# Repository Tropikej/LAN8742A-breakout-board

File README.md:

<h1 align="center">LAN8742A-breakout-board</h1>

<p align="center" width="100%">
  
</p>

***

<p align="center">
  
&nbsp; &nbsp; &nbsp; &nbsp;
  
</p>

***

## SPECIFICATIONS

| Parameter | Value | 
| --- | --- |
| Dimensions | 40.0 × 50.0 mm |

***

## DIRECTORY STRUCTURE

    .
    ├─ Computations       # Misc calculations
    ├─ HTML               # HTML files for generated webpage
    ├─ Images             # Pictures and renders
    │
    ├─ kibot_resources    # External resources for KiBot
    │  ├─ colors          # Color theme for KiCad
    │  ├─ fonts           # Fonts used in the project
    │  ├─ scripts         # External scripts used with KiBot
    │  └─ templates       # Templates for KiBot generated reports
    │
    ├─ kibot_yaml         # KiBot YAML config files
    ├─ KiRI               # KiRI (PCB diff viewer) files
    │
    ├─ lib                # KiCad footprint and symbol libraries
    │  ├─ 3d_models       # Component 3D models
    │  ├─ lib_fp          # Footprint libraries
    │  └─ lib_sym         # Symbol libraries
    │
    ├─ Logos              # Logos
    │
    ├─ Manufacturing      # Assembly and fabrication documents
    │  ├─ Assembly        # Assembly documents (BoM, pos, notes)
    │  │
    │  └─ Fabrication     # Fabrication documents (ZIP, notes)
    │     ├─ Drill Tables # CSV drill tables
    │     └─ Gerbers      # Gerbers
    │
    ├─ Report             # Reports for ERC/DRC
    ├─ Schematic          # PDF of schematic
    ├─ Templates          # Title block templates
    ├─ Testing
    │  └─ Testpoints      # Testpoints tables      
    │
    └─ Variants           # Outputs for assembly variants

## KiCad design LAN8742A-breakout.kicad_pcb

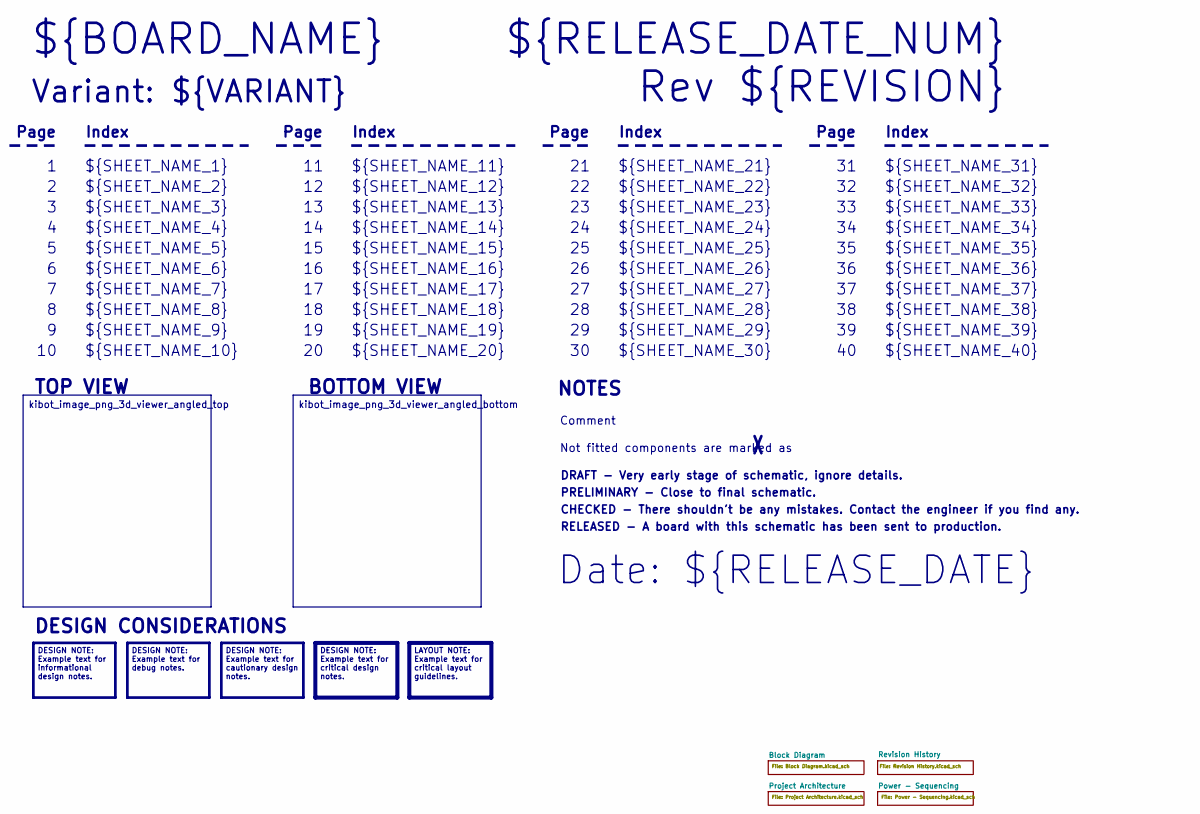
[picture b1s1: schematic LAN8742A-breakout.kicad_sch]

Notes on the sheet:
DESIGN NOTE: Example text for cautionary design notes.
DESIGN NOTE: Example text for debug notes.
DESIGN NOTE: Example text for critical design notes.
LAYOUT NOTE: Example text for critical layout guidelines.
kibot_image_png_3d_viewer_angled_bottom
DESIGN NOTE: Example text for informational design notes.
kibot_image_png_3d_viewer_angled_top
Variant: ${VARIANT}
RELEASED - A board with this schematic has been sent to production.
${SHEET_NAME_24}
Index
Page
PRELIMINARY - Close to final schematic.
${SHEET_NAME_22}
DRAFT - Very early stage of schematic, ignore details.
${SHEET_NAME_12}
${SHEET_NAME_8}
${SHEET_NAME_2}
${SHEET_NAME_5}
${SHEET_NAME_20}
${SHEET_NAME_23}
${RELEASE_DATE_NUM}
${SHEET_NAME_35}
Not fitted components are marked as
${SHEET_NAME_11}
${SHEET_NAME_6}
${SHEET_NAME_37}
${SHEET_NAME_26}
${SHEET_NAME_36}
Rev ${REVISION}
${SHEET_NAME_15}
CHECKED - There shouldn't be any mistakes. Contact the engineer if you find any.
BOTTOM VIEW
${SHEET_NAME_14}
${SHEET_NAME_21}
${SHEET_NAME_17}
${SHEET_NAME_18}
Date: ${RELEASE_DATE}
${SHEET_NAME_7}
${SHEET_NAME_31}

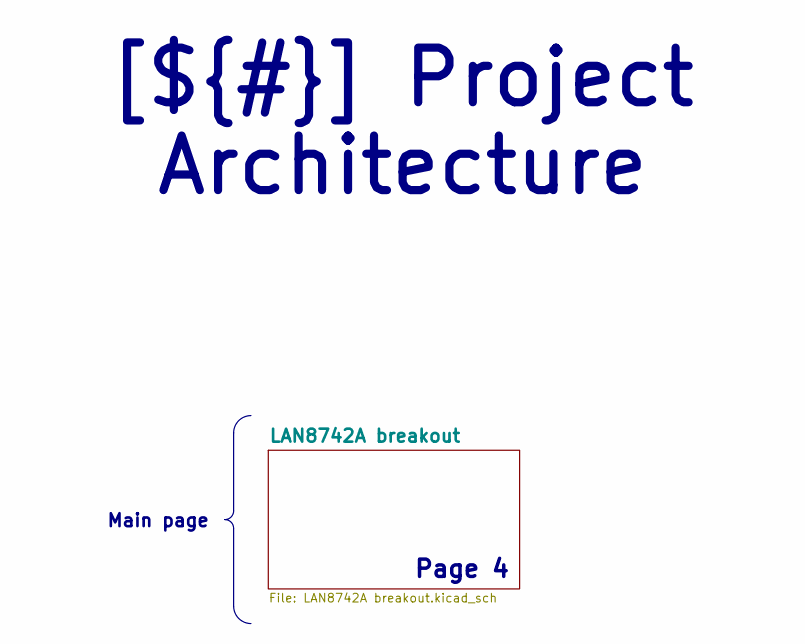
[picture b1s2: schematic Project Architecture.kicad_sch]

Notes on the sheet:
Main page
[${#}] ${TITLE}
Page 4

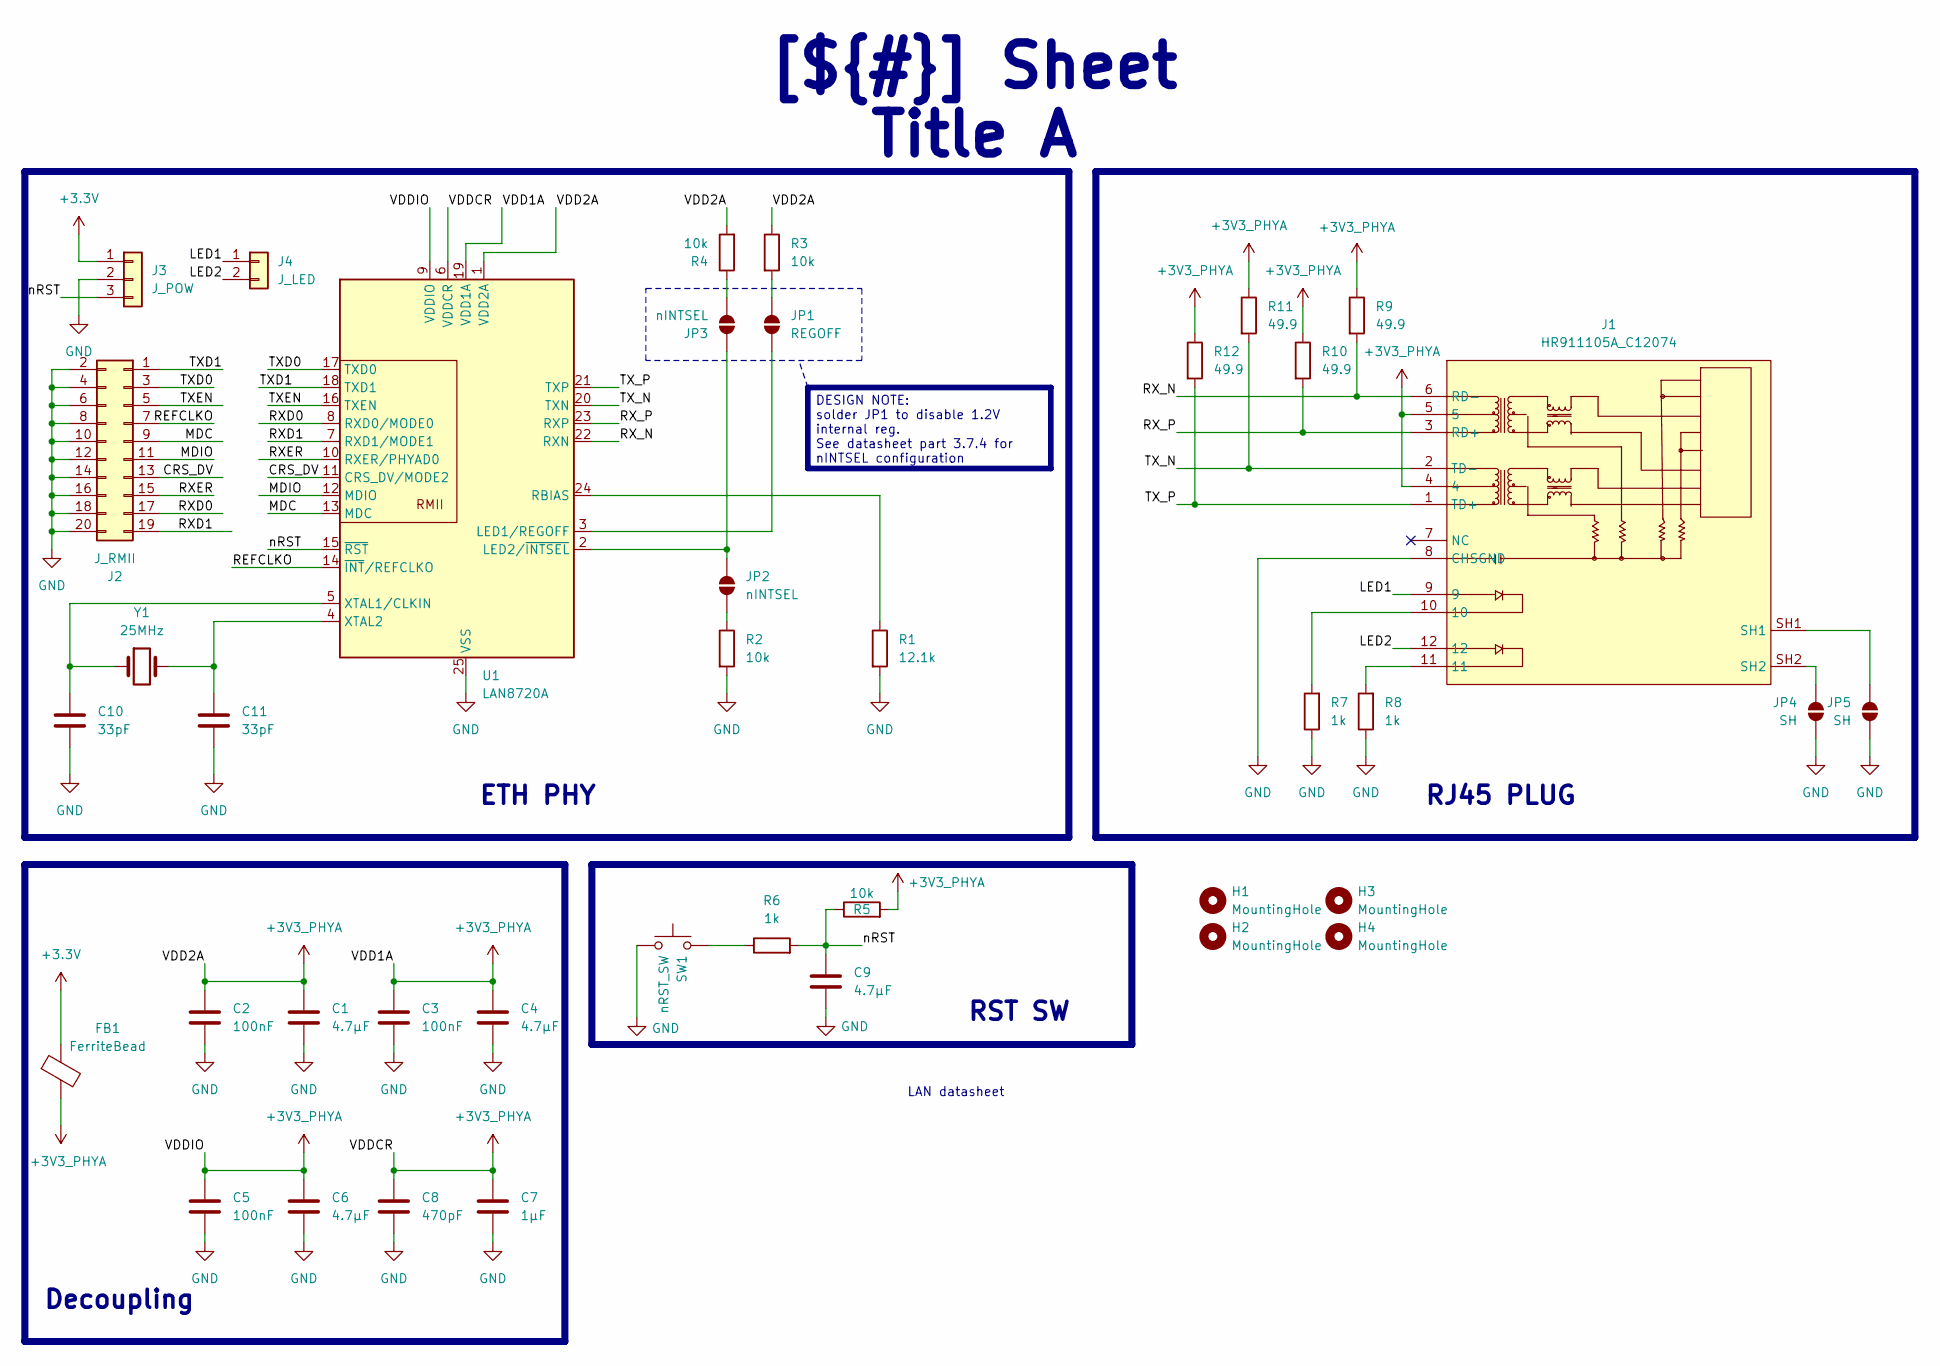
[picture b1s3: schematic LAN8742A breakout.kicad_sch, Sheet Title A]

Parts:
C1, C4, C6, C9: 4.7µF; C_0603_1608Metric_Pad1.08x0.95mm_HandSolder; Manufacturer Part Number CL10A475KA8NQNC; LCSC C69335
C2, C3, C5: 100nF; C_0603_1608Metric_Pad1.08x0.95mm_HandSolder; Manufacturer Part Number CC0603KRX7R9BB104; LCSC C14663
C7: 1µF; C_0603_1608Metric_Pad1.08x0.95mm_HandSolder; Manufacturer Part Number CL10B105KA8NNNC; LCSC C29936
C8: 470pF; C_0603_1608Metric_Pad1.08x0.95mm_HandSolder; Manufacturer Part Number 0603CG471J500NT; LCSC C36252
C10, C11: 33pF; C_0603_1608Metric_Pad1.08x0.95mm_HandSolder; Manufacturer Part Number CC0603JRNPO9BN330; LCSC C107047
FB1: FerriteBead; L0603; Manufacturer Part Number BLM18PG121SN1D; LCSC C14709
H1, H2, H3, H4: MountingHole; MountingHole_3.2mm_M3_DIN965
J1: HR911105A_C12074; RJ45-TH_HR911105A; LCSC C12074
J2: J_RMII; PinHeader_2x10_P2.54mm_Vertical
J3: J_POW; PinHeader_1x03_P2.54mm_Vertical
J4: J_LED; PinHeader_1x02_P2.54mm_Vertical
JP1: REGOFF; SolderJumper-2_P1.3mm_Open_RoundedPad1.0x1.5mm
JP2: nINTSEL; SolderJumper-2_P1.3mm_Bridged_RoundedPad1.0x1.5mm
JP3: nINTSEL; SolderJumper-2_P1.3mm_Open_RoundedPad1.0x1.5mm
JP4, JP5: SH; SolderJumper-2_P1.3mm_Bridged_RoundedPad1.0x1.5mm
R1: 12.1k; R_0603_1608Metric_Pad0.98x0.95mm_HandSolder; Manufacturer Part Number 0603WAF1212T5E; LCSC C22864
R2, R3, R4, R5: 10k; R_0603_1608Metric_Pad0.98x0.95mm_HandSolder; Manufacturer Part Number RC0603FR-0710KL; LCSC C98220
R6, R7, R8: 1k; R_0603_1608Metric_Pad0.98x0.95mm_HandSolder; Manufacturer Part Number RC0603FR-071KL; LCSC C22548
R9, R10, R11, R12: 49.9; R_0603_1608Metric_Pad0.98x0.95mm_HandSolder; Manufacturer Part Number RC0603FR-0749R9L; LCSC C114625
SW1: nRST_SW; SW_PUSH_6mm
U1: LAN8720A; VQFN-24-1EP_4x4mm_P0.5mm_EP2.5x2.5mm_ThermalVias; Manufacturer Part Number LAN8742A-CZ-TR; LCSC C510876
Y1: 25MHz; 01.X.SD.120MMOI025000000; Manufacturer Part Number 01.X.SD.120MMOI025000000; LCSC C7462598

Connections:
+3.3V: FB1.1, J3.1
+3V3_PHYA: C1.1, C2.1, C3.1, C4.1, C5.1, C6.1, C7.1, C8.1, FB1.2, J1.4, J1.5, R3.1, R4.2, R5.2, R9.1, R10.1, R11.1, R12.1, U1.1 (VDD2A), U1.6 (VDDCR), U1.9 (VDDIO), U1.19 (VDD1A)
/Project Architecture/LAN8742A breakout/CRS_DV: J2.13, U1.11 (CRS_DV/MODE2)
/Project Architecture/LAN8742A breakout/LED1: J1.9, J4.1
/Project Architecture/LAN8742A breakout/LED2: J1.12, J4.2
/Project Architecture/LAN8742A breakout/MDC: J2.9, U1.13 (MDC)
/Project Architecture/LAN8742A breakout/MDIO: J2.11, U1.12 (MDIO)
/Project Architecture/LAN8742A breakout/REFCLKO: J2.7, U1.14 (~INT/REFCLKO)
/Project Architecture/LAN8742A breakout/RXD0: J2.17, U1.8 (RXD0/MODE0)
/Project Architecture/LAN8742A breakout/RXD1: J2.19, U1.7 (RXD1/MODE1)
/Project Architecture/LAN8742A breakout/RXER: J2.15, U1.10 (RXER/PHYAD0)
/Project Architecture/LAN8742A breakout/RX_N: J1.6 (RD-), R9.2, U1.22 (RXN)
/Project Architecture/LAN8742A breakout/RX_P: J1.3 (RD+), R10.2, U1.23 (RXP)
/Project Architecture/LAN8742A breakout/TXD0: J2.3, U1.17 (TXD0)
/Project Architecture/LAN8742A breakout/TXD1: J2.1, U1.18 (TXD1)
/Project Architecture/LAN8742A breakout/TXEN: J2.5, U1.16 (TXEN)
/Project Architecture/LAN8742A breakout/TX_N: J1.2 (TD-), R11.2, U1.20 (TXN)
/Project Architecture/LAN8742A breakout/TX_P: J1.1 (TD+), R12.2, U1.21 (TXP)
/Project Architecture/LAN8742A breakout/nRST: C9.1, J3.3, R5.1, R6.2, U1.15 (~RST)
GND: C1.2, C2.2, C3.2, C4.2, C5.2, C6.2, C7.2, C8.2, C9.2, C10.2, C11.2, J1.8 (CHSGND), J2.2, J2.4, J2.6, J2.8, J2.10, J2.12, J2.14, J2.16, J2.18, J2.20, J3.2, JP4.1 (A), JP5.1 (A), R1.2, R2.2, R7.1, R8.1, SW1.1, U1.25 (VSS)
unnamed: J1.10, R7.2
unnamed: J1.11, R8.2
unnamed: JP1.1 (A), U1.3 (LED1/REGOFF)
unnamed: JP1.2 (B), R3.2
unnamed: JP2.1 (A), R2.1
unnamed: JP2.2 (B), JP3.2 (B), U1.2 (LED2/~INTSEL)
unnamed: JP3.1 (A), R4.1
unnamed: J1.SH2, JP4.2 (B)
unnamed: J1.SH1, JP5.2 (B)
unnamed: R6.1, SW1.2
unnamed: R1.1, U1.24 (RBIAS)
unnamed: C10.1, U1.5 (XTAL1/CLKIN), Y1.1
unnamed: C11.1, U1.4 (XTAL2), Y1.2

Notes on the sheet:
[${#}] ${TITLE}
Decoupling
ETH PHY
RJ45 PLUG
RST SW
DESIGN NOTE: solder JP1 to disable 1.2V internal reg. See datasheet part 3.7.4 for nINTSEL configuration
LAN datasheet

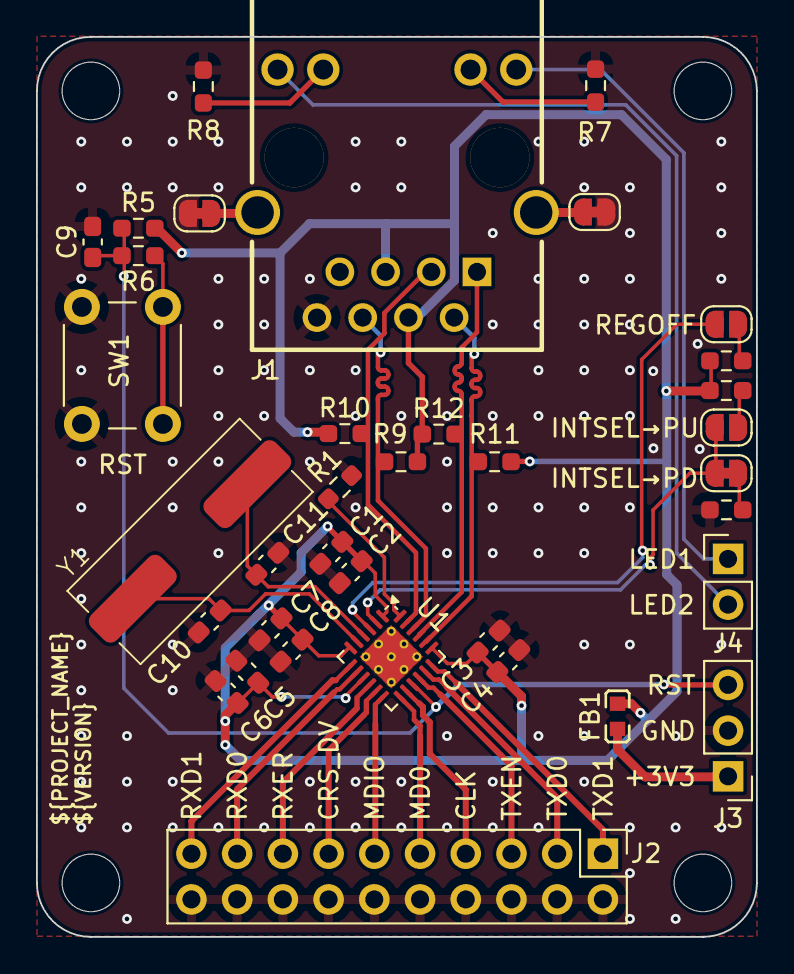
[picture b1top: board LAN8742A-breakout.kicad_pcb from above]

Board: 4 copper layers, 40.0 x 50.0 mm, 40 parts (0 on the bottom side), 33 nets.

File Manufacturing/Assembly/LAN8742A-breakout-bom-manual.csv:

"#","Qty","Reference","Value","Manufacturer Part Number","LCSC"
"1","4","R9,R10,R11,R12","49.9","RC0603FR-0749R9L","C114625"
"2","3","R6,R7,R8","1k","RC0603FR-071KL","C22548"
"3","4","R2,R3,R4,R5","10k","RC0603FR-0710KL","C98220"
"4","1","R1","12.1k","0603WAF1212T5E","C22864"
"5","1","U1","LAN8720A","LAN8742A-CZ-TR","C510876"
"6","2","C10,C11","33pF","CC0603JRNPO9BN330","C107047"
"7","1","C8","470pF","0603CG471J500NT","C36252"
"8","1","C7","1µF","CL10B105KA8NNNC","C29936"
"9","3","C2,C3,C5","100nF","CC0603KRX7R9BB104","C14663"
"10","4","C1,C4,C6,C9","4.7µF","CL10A475KA8NQNC","C69335"
"11","1","FB1","FerriteBead","BLM18PG121SN1D","C14709"
"12","1","Y1","25MHz","01.X.SD.120MMOI025000000","C7462598"
"13","1","J1","HR911105A_C12074","","C12074"

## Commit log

2025-10-05 Update Outputs
2025-10-05 added PHY & RJ45 plug
2025-10-07 routed signals
2025-10-07 update routing
2025-10-08 changed kibot project type to PRELIMINARY
2025-10-08 finished routing & added silkscreen
2025-10-09 stitching vias
